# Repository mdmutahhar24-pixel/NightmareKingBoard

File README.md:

# NightmareKingBoard
A TKL Keyboard based of the Hollow Knight boss Nightmare King Grimm. (Very bad representation)

This keyboard features a red and black case, with RGB lighting, and a rotary encoder. This was coded with QMK firmware.

For more information, please check out the BOM or the Journals.

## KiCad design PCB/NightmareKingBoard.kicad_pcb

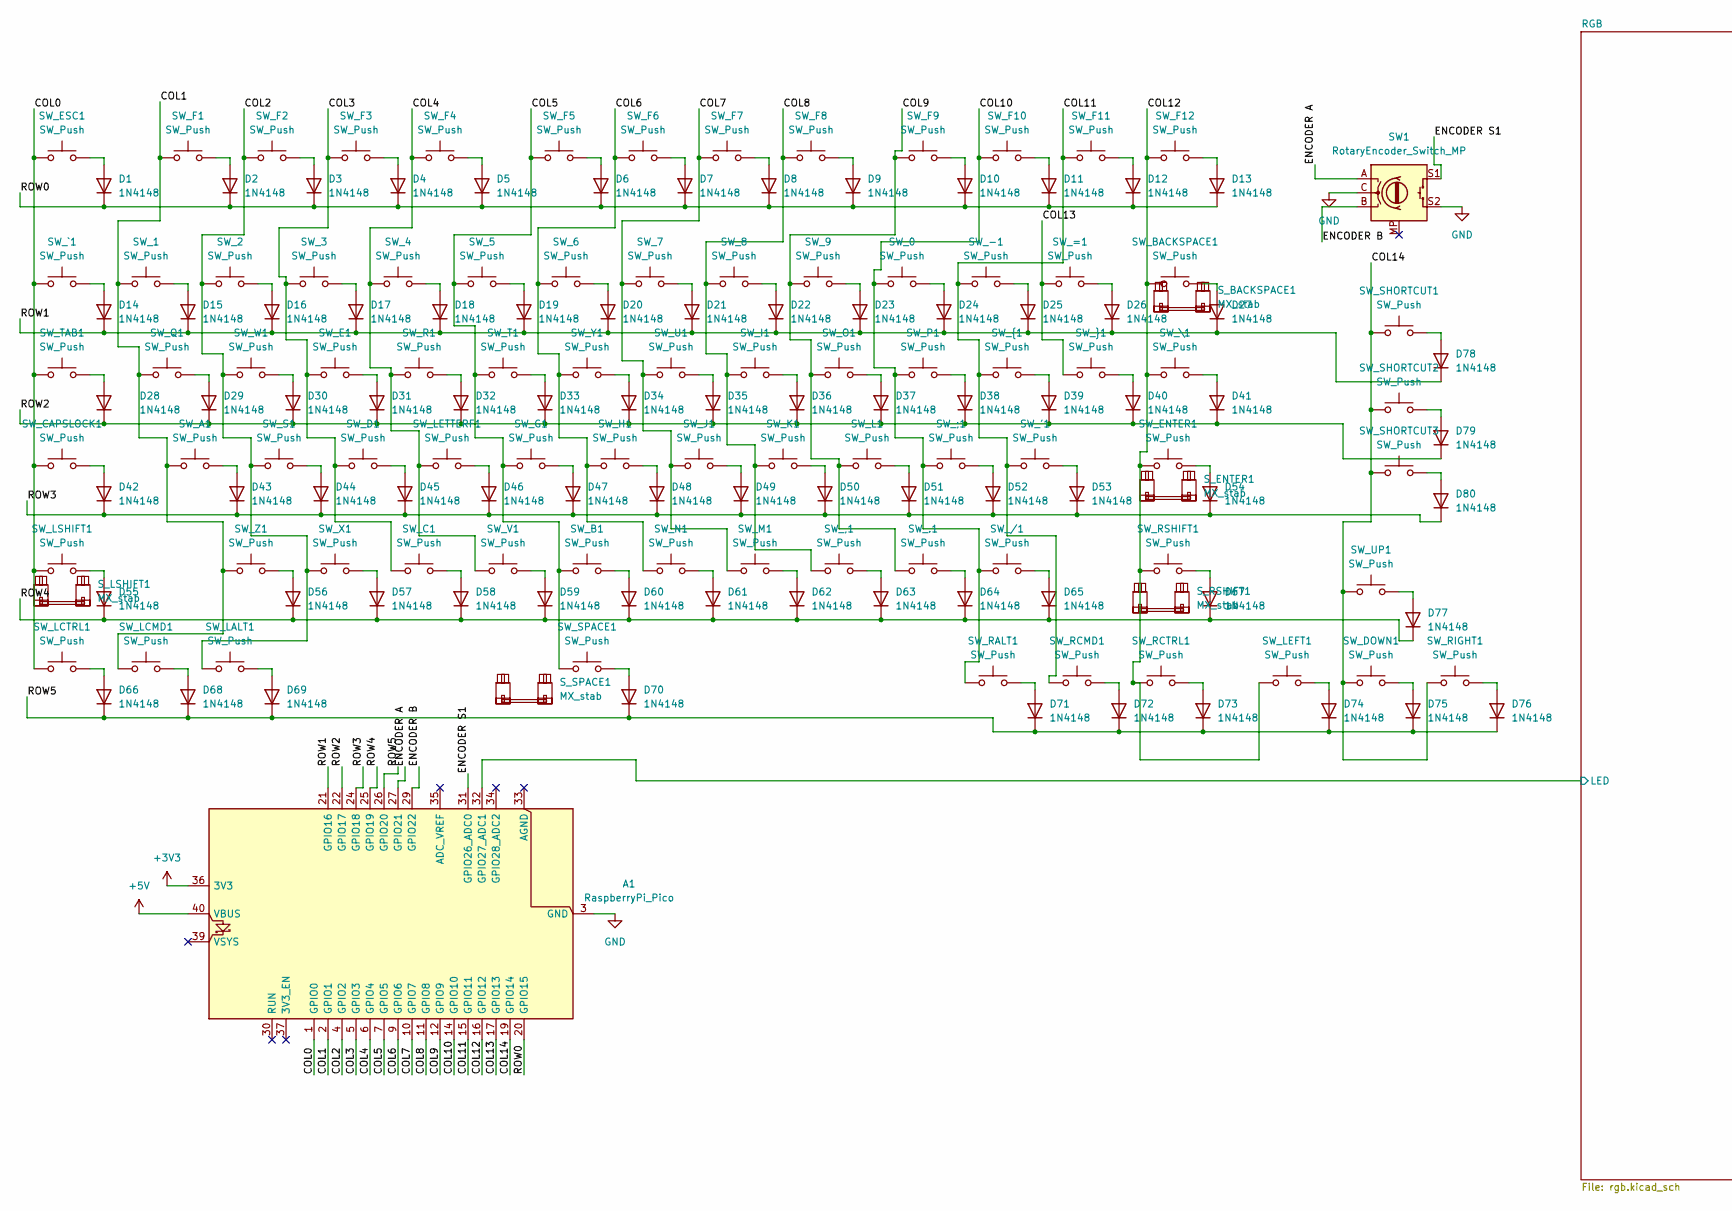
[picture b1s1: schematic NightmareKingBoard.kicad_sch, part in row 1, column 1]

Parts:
A1: RaspberryPi_Pico; RaspberryPi_Pico_Common_THT
D1, D2, D3, D4, D5, D6, D7, D8, D9, D10, D11, D12, D13, D14, D15, D16, D17, D18, D19, D20, D21, D22, D23, D24, D25, D26, D27, D28, D29, D30, D31, D32, D33, D34, D35, D36, D37, D38, D39, D40, D41, D42, D43, D44, D45, D46, D47, D48, D49, D50, D51, D52, D53, D54, D55, D56, D57, D58, D59, D60, D61, D62, D63, D64, D65, D66, D67, D68, D69, D70, D71, D72, D73, D74, D75, D76, D77, D78, D79, D80: 1N4148; D_DO-35_SOD27_P7.62mm_Horizontal
SW1: RotaryEncoder_Switch_MP; RotaryEncoder_Alps_EC11E-Switch_Vertical_H20mm
SW_0, SW_1, SW_2, SW_3, SW_4, SW_5, SW_6, SW_7, SW_8, SW_9, SW_.1: SW_Push; SW_MX_1u
SW_'1: SW_Push; SW_MX_1u
SW_,1: SW_Push; SW_MX_1u
SW_-1: SW_Push; SW_MX_1u
SW_/1: SW_Push; SW_MX_1u
SW_;1: SW_Push; SW_MX_1u
SW_=1: SW_Push; SW_MX_1u
SW_A1: SW_Push; SW_MX_1u
SW_B1: SW_Push; SW_MX_1u
SW_BACKSPACE1: SW_Push; SW_MX_1u
SW_C1: SW_Push; SW_MX_1u
SW_CAPSLOCK1: SW_Push; SW_MX_1.75u
SW_D1: SW_Push; SW_MX_1u
SW_DOWN1: SW_Push; SW_MX_1u
SW_E1: SW_Push; SW_MX_1u
SW_ENTER1: SW_Push; SW_MX_1u
SW_ESC1: SW_Push; SW_MX_1u
SW_F1, SW_F2, SW_F3, SW_F4, SW_F5, SW_F6, SW_F7, SW_F8, SW_F9, SW_F10, SW_F11, SW_F12: SW_Push; SW_MX_1u
SW_G1: SW_Push; SW_MX_1u
SW_H1: SW_Push; SW_MX_1u
SW_I1: SW_Push; SW_MX_1u
SW_J1: SW_Push; SW_MX_1u
SW_K1: SW_Push; SW_MX_1u
SW_L1: SW_Push; SW_MX_1u
SW_LALT1: SW_Push; SW_MX_1u
SW_LCMD1: SW_Push; SW_MX_1u
SW_LCTRL1: SW_Push; SW_MX_1u
SW_LEFT1: SW_Push; SW_MX_1u
SW_LETTERF1: SW_Push; SW_MX_1u
SW_LSHIFT1: SW_Push; SW_MX_1u
SW_M1: SW_Push; SW_MX_1u
SW_N1: SW_Push; SW_MX_1u
SW_O1: SW_Push; SW_MX_1u
SW_P1: SW_Push; SW_MX_1u
SW_Q1: SW_Push; SW_MX_1u
SW_R1: SW_Push; SW_MX_1u
SW_RALT1: SW_Push; SW_MX_1u
SW_RCMD1: SW_Push; SW_MX_1u
SW_RCTRL1: SW_Push; SW_MX_1u
SW_RIGHT1: SW_Push; SW_MX_1u
SW_RSHIFT1: SW_Push; SW_MX_1u
SW_S1: SW_Push; SW_MX_1u
SW_SHORTCUT1, SW_SHORTCUT2, SW_SHORTCUT3: SW_Push; SW_MX_1u
SW_SPACE1: SW_Push; SW_MX_1u
SW_T1: SW_Push; SW_MX_1u
SW_TAB1: SW_Push; SW_MX_1.5u
SW_U1: SW_Push; SW_MX_1u
SW_UP1: SW_Push; SW_MX_1u
SW_V1: SW_Push; SW_MX_1u
SW_W1: SW_Push; SW_MX_1u
SW_X1: SW_Push; SW_MX_1u
SW_Y1: SW_Push; SW_MX_1u
SW_Z1: SW_Push; SW_MX_1u
SW_\1: SW_Push; SW_MX_1u
SW_`1: SW_Push; SW_MX_1u
SW_{1: SW_Push; SW_MX_1u
SW_}1: SW_Push; SW_MX_1u
S_BACKSPACE1: MX_stab; STAB_MX_2u
S_ENTER1: MX_stab; STAB_MX_2.25u
S_LSHIFT1: MX_stab; STAB_MX_2.25u
S_RSHIFT1: MX_stab; STAB_MX_2.25u
S_SPACE1: MX_stab; STAB_MX_P_6.25u

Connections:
+3V3: A1.36 (3V3)
+5V: A1.40 (VBUS); also elsewhere on the board
/COL0: A1.1 (GPIO0), SW_CAPSLOCK1.1, SW_ESC1.1, SW_LCTRL1.1, SW_LSHIFT1.1, SW_TAB1.1, SW_`1.1
/COL1: A1.2 (GPIO1), SW_1.1, SW_A1.1, SW_F1.1, SW_LCMD1.1, SW_Q1.1, SW_Z1.1
/COL2: A1.4 (GPIO2), SW_2.1, SW_F2.1, SW_LALT1.1, SW_S1.1, SW_W1.1, SW_X1.1
/COL3: A1.5 (GPIO3), SW_3.1, SW_C1.1, SW_D1.1, SW_E1.1, SW_F3.1
/COL4: A1.6 (GPIO4), SW_4.1, SW_F4.1, SW_LETTERF1.1, SW_R1.1, SW_V1.1
/COL5: A1.7 (GPIO5), SW_5.1, SW_B1.1, SW_F5.1, SW_G1.1, SW_SPACE1.1, SW_T1.1
/COL6: A1.9 (GPIO6), SW_6.1, SW_F6.1, SW_H1.1, SW_N1.1, SW_Y1.1
/COL7: A1.10 (GPIO7), SW_7.1, SW_F7.1, SW_J1.1, SW_M1.1, SW_U1.1
/COL8: A1.11 (GPIO8), SW_8.1, SW_,1.1, SW_F8.1, SW_I1.1, SW_K1.1
/COL9: A1.12 (GPIO9), SW_9.1, SW_.1.1, SW_F9.1, SW_L1.1, SW_O1.1
/COL10: A1.14 (GPIO10), SW_0.1, SW_/1.1, SW_;1.1, SW_F10.1, SW_P1.1, SW_RALT1.1
/COL11: A1.15 (GPIO11), SW_'1.1, SW_-1.1, SW_F11.1, SW_RCMD1.1, SW_{1.1
/COL12: A1.16 (GPIO12), SW_BACKSPACE1.1, SW_ENTER1.1, SW_F12.1, SW_LEFT1.1, SW_RCTRL1.1, SW_RSHIFT1.1, SW_\1.1
/COL13: A1.17 (GPIO13), SW_=1.1, SW_}1.1
/COL14: A1.19 (GPIO14), SW_DOWN1.1, SW_RIGHT1.1, SW_SHORTCUT1.1, SW_SHORTCUT2.1, SW_SHORTCUT3.1, SW_UP1.1
/ENCODER A: A1.27 (GPIO21), SW1.A
/ENCODER B: A1.29 (GPIO22), SW1.B
/ENCODER S1: A1.31 (GPIO26_ADC0), SW1.S1
/RGB/LED: A1.32 (GPIO27_ADC1); also elsewhere on the board
/ROW0: A1.20 (GPIO15), D1.1 (K), D2.1 (K), D3.1 (K), D4.1 (K), D5.1 (K), D6.1 (K), D7.1 (K), D8.1 (K), D9.1 (K), D10.1 (K), D11.1 (K), D12.1 (K), D13.1 (K)
/ROW1: A1.21 (GPIO16), D14.1 (K), D15.1 (K), D16.1 (K), D17.1 (K), D18.1 (K), D19.1 (K), D20.1 (K), D21.1 (K), D22.1 (K), D23.1 (K), D24.1 (K), D25.1 (K), D26.1 (K), D27.1 (K), D78.1 (K)
/ROW2: A1.22 (GPIO17), D28.1 (K), D29.1 (K), D30.1 (K), D31.1 (K), D32.1 (K), D33.1 (K), D34.1 (K), D35.1 (K), D36.1 (K), D37.1 (K), D38.1 (K), D39.1 (K), D40.1 (K), D41.1 (K), D79.1 (K)
/ROW3: A1.24 (GPIO18), D42.1 (K), D43.1 (K), D44.1 (K), D45.1 (K), D46.1 (K), D47.1 (K), D48.1 (K), D49.1 (K), D50.1 (K), D51.1 (K), D52.1 (K), D53.1 (K), D54.1 (K), D80.1 (K)
/ROW4: A1.25 (GPIO19), D55.1 (K), D56.1 (K), D57.1 (K), D58.1 (K), D59.1 (K), D60.1 (K), D61.1 (K), D62.1 (K), D63.1 (K), D64.1 (K), D65.1 (K), D67.1 (K), D77.1 (K)
/ROW5: A1.26 (GPIO20), D66.1 (K), D68.1 (K), D69.1 (K), D70.1 (K), D71.1 (K), D72.1 (K), D73.1 (K), D74.1 (K), D75.1 (K), D76.1 (K)
GND: A1.3 (GND), A1.8 (GND), A1.13 (GND), A1.18 (GND), A1.23 (GND), A1.28 (GND), A1.38 (GND), SW1.C, SW1.S2; also elsewhere on the board
unnamed: D1.2 (A), SW_ESC1.2
unnamed: D2.2 (A), SW_F1.2
unnamed: D3.2 (A), SW_F2.2
unnamed: D4.2 (A), SW_F3.2
unnamed: D5.2 (A), SW_F4.2
unnamed: D6.2 (A), SW_F5.2
unnamed: D7.2 (A), SW_F6.2
unnamed: D8.2 (A), SW_F7.2
unnamed: D9.2 (A), SW_F8.2
unnamed: D10.2 (A), SW_F9.2
unnamed: D11.2 (A), SW_F10.2
unnamed: D12.2 (A), SW_F11.2
unnamed: D13.2 (A), SW_F12.2
unnamed: D14.2 (A), SW_`1.2
unnamed: D15.2 (A), SW_1.2
unnamed: D16.2 (A), SW_2.2
unnamed: D17.2 (A), SW_3.2
unnamed: D18.2 (A), SW_4.2
unnamed: D19.2 (A), SW_5.2
unnamed: D20.2 (A), SW_6.2
unnamed: D21.2 (A), SW_7.2
unnamed: D22.2 (A), SW_8.2
unnamed: D23.2 (A), SW_9.2
unnamed: D24.2 (A), SW_0.2
unnamed: D25.2 (A), SW_-1.2
unnamed: D26.2 (A), SW_=1.2
unnamed: D27.2 (A), SW_BACKSPACE1.2
unnamed: D28.2 (A), SW_TAB1.2
unnamed: D29.2 (A), SW_Q1.2
unnamed: D30.2 (A), SW_W1.2
unnamed: D31.2 (A), SW_E1.2
unnamed: D32.2 (A), SW_R1.2
unnamed: D33.2 (A), SW_T1.2
unnamed: D34.2 (A), SW_Y1.2
unnamed: D35.2 (A), SW_U1.2
unnamed: D36.2 (A), SW_I1.2
unnamed: D37.2 (A), SW_O1.2
unnamed: D38.2 (A), SW_P1.2
unnamed: D39.2 (A), SW_{1.2
unnamed: D40.2 (A), SW_}1.2
unnamed: D41.2 (A), SW_\1.2
unnamed: D42.2 (A), SW_CAPSLOCK1.2
unnamed: D43.2 (A), SW_A1.2
unnamed: D44.2 (A), SW_S1.2
unnamed: D45.2 (A), SW_D1.2
unnamed: D46.2 (A), SW_LETTERF1.2
unnamed: D47.2 (A), SW_G1.2
unnamed: D48.2 (A), SW_H1.2
unnamed: D49.2 (A), SW_J1.2
unnamed: D50.2 (A), SW_K1.2
unnamed: D51.2 (A), SW_L1.2
unnamed: D52.2 (A), SW_;1.2
unnamed: D53.2 (A), SW_'1.2
unnamed: D54.2 (A), SW_ENTER1.2
unnamed: D55.2 (A), SW_LSHIFT1.2
unnamed: D56.2 (A), SW_Z1.2
unnamed: D57.2 (A), SW_X1.2
unnamed: D58.2 (A), SW_C1.2
unnamed: D59.2 (A), SW_V1.2
unnamed: D60.2 (A), SW_B1.2
unnamed: D61.2 (A), SW_N1.2
unnamed: D62.2 (A), SW_M1.2
unnamed: D63.2 (A), SW_,1.2
unnamed: D64.2 (A), SW_.1.2
unnamed: D65.2 (A), SW_/1.2
unnamed: D66.2 (A), SW_LCTRL1.2
unnamed: D67.2 (A), SW_RSHIFT1.2
unnamed: D68.2 (A), SW_LCMD1.2
unnamed: D69.2 (A), SW_LALT1.2
unnamed: D70.2 (A), SW_SPACE1.2
unnamed: D71.2 (A), SW_RALT1.2
unnamed: D72.2 (A), SW_RCMD1.2
unnamed: D73.2 (A), SW_RCTRL1.2
unnamed: D74.2 (A), SW_LEFT1.2
unnamed: D75.2 (A), SW_DOWN1.2
unnamed: D76.2 (A), SW_RIGHT1.2
unnamed: D77.2 (A), SW_UP1.2
unnamed: D78.2 (A), SW_SHORTCUT1.2
unnamed: D79.2 (A), SW_SHORTCUT2.2
unnamed: D80.2 (A), SW_SHORTCUT3.2

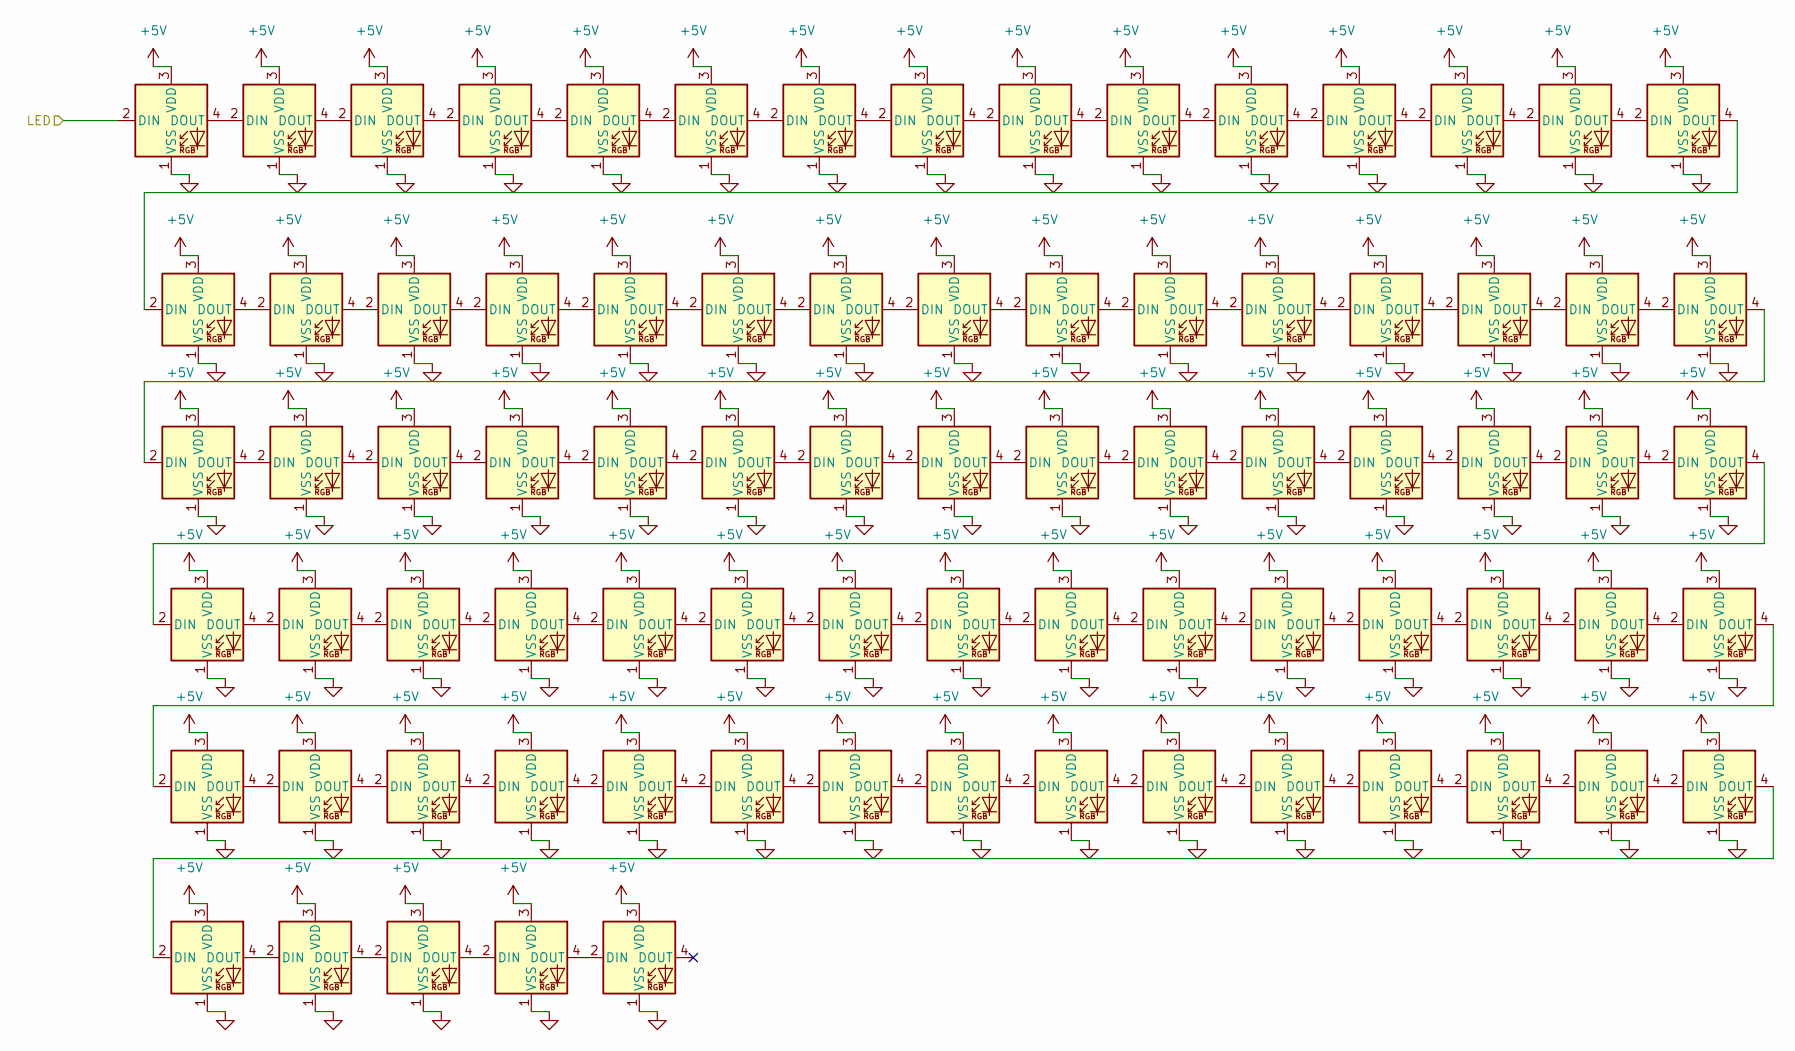
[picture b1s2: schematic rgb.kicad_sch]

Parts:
D81, D82, D83, D84, D85, D86, D87, D88, D89, D90, D91, D92, D93, D94, D95, D96, D97, D98, D99, D100, D101, D102, D103, D104, D105, D106, D107, D108, D109, D110, D111, D112, D113, D114, D115, D116, D117, D118, D119, D120, D121, D122, D123, D124, D125, D126, D127, D128, D129, D130, D131, D132, D133, D134, D135, D136, D137, D138, D139, D140, D141, D142, D143, D144, D145, D146, D147, D148, D149, D150, D151, D152, D153, D154, D155, D156, D157, D158, D159, D160: SK6812MINI-E; LED_SK6812MINI-E_3.2x2.8mm_P1.5mm_ReverseMount

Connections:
+5V: D81.3 (VDD), D82.3 (VDD), D83.3 (VDD), D84.3 (VDD), D85.3 (VDD), D86.3 (VDD), D87.3 (VDD), D88.3 (VDD), D89.3 (VDD), D90.3 (VDD), D91.3 (VDD), D92.3 (VDD), D93.3 (VDD), D94.3 (VDD), D95.3 (VDD), D96.3 (VDD), D97.3 (VDD), D98.3 (VDD), D99.3 (VDD), D100.3 (VDD), D101.3 (VDD), D102.3 (VDD), D103.3 (VDD), D104.3 (VDD), D105.3 (VDD), D106.3 (VDD), D107.3 (VDD), D108.3 (VDD), D109.3 (VDD), D110.3 (VDD), D111.3 (VDD), D112.3 (VDD), D113.3 (VDD), D114.3 (VDD), D115.3 (VDD), D116.3 (VDD), D117.3 (VDD), D118.3 (VDD), D119.3 (VDD), D120.3 (VDD), D121.3 (VDD), D122.3 (VDD), D123.3 (VDD), D124.3 (VDD), D125.3 (VDD), D126.3 (VDD), D127.3 (VDD), D128.3 (VDD), D129.3 (VDD), D130.3 (VDD), D131.3 (VDD), D132.3 (VDD), D133.3 (VDD), D134.3 (VDD), D135.3 (VDD), D136.3 (VDD), D137.3 (VDD), D138.3 (VDD), D139.3 (VDD), D140.3 (VDD), D141.3 (VDD), D142.3 (VDD), D143.3 (VDD), D144.3 (VDD), D145.3 (VDD), D146.3 (VDD), D147.3 (VDD), D148.3 (VDD), D149.3 (VDD), D150.3 (VDD), D151.3 (VDD), D152.3 (VDD), D153.3 (VDD), D154.3 (VDD), D155.3 (VDD), D156.3 (VDD), D157.3 (VDD), D158.3 (VDD), D159.3 (VDD), D160.3 (VDD); also elsewhere on the board
/RGB/LED: D81.2 (DIN); also elsewhere on the board
GND: D81.1 (VSS), D82.1 (VSS), D83.1 (VSS), D84.1 (VSS), D85.1 (VSS), D86.1 (VSS), D87.1 (VSS), D88.1 (VSS), D89.1 (VSS), D90.1 (VSS), D91.1 (VSS), D92.1 (VSS), D93.1 (VSS), D94.1 (VSS), D95.1 (VSS), D96.1 (VSS), D97.1 (VSS), D98.1 (VSS), D99.1 (VSS), D100.1 (VSS), D101.1 (VSS), D102.1 (VSS), D103.1 (VSS), D104.1 (VSS), D105.1 (VSS), D106.1 (VSS), D107.1 (VSS), D108.1 (VSS), D109.1 (VSS), D110.1 (VSS), D111.1 (VSS), D112.1 (VSS), D113.1 (VSS), D114.1 (VSS), D115.1 (VSS), D116.1 (VSS), D117.1 (VSS), D118.1 (VSS), D119.1 (VSS), D120.1 (VSS), D121.1 (VSS), D122.1 (VSS), D123.1 (VSS), D124.1 (VSS), D125.1 (VSS), D126.1 (VSS), D127.1 (VSS), D128.1 (VSS), D129.1 (VSS), D130.1 (VSS), D131.1 (VSS), D132.1 (VSS), D133.1 (VSS), D134.1 (VSS), D135.1 (VSS), D136.1 (VSS), D137.1 (VSS), D138.1 (VSS), D139.1 (VSS), D140.1 (VSS), D141.1 (VSS), D142.1 (VSS), D143.1 (VSS), D144.1 (VSS), D145.1 (VSS), D146.1 (VSS), D147.1 (VSS), D148.1 (VSS), D149.1 (VSS), D150.1 (VSS), D151.1 (VSS), D152.1 (VSS), D153.1 (VSS), D154.1 (VSS), D155.1 (VSS), D156.1 (VSS), D157.1 (VSS), D158.1 (VSS), D159.1 (VSS), D160.1 (VSS); also elsewhere on the board
unnamed: D81.4 (DOUT), D82.2 (DIN)
unnamed: D82.4 (DOUT), D83.2 (DIN)
unnamed: D83.4 (DOUT), D84.2 (DIN)
unnamed: D84.4 (DOUT), D85.2 (DIN)
unnamed: D85.4 (DOUT), D86.2 (DIN)
unnamed: D86.4 (DOUT), D87.2 (DIN)
unnamed: D87.4 (DOUT), D88.2 (DIN)
unnamed: D88.4 (DOUT), D89.2 (DIN)
unnamed: D89.4 (DOUT), D90.2 (DIN)
unnamed: D90.4 (DOUT), D91.2 (DIN)
unnamed: D91.4 (DOUT), D92.2 (DIN)
unnamed: D92.4 (DOUT), D93.2 (DIN)
unnamed: D93.4 (DOUT), D94.2 (DIN)
unnamed: D94.4 (DOUT), D95.2 (DIN)
unnamed: D95.4 (DOUT), D96.2 (DIN)
unnamed: D96.4 (DOUT), D97.2 (DIN)
unnamed: D97.4 (DOUT), D98.2 (DIN)
unnamed: D98.4 (DOUT), D99.2 (DIN)
unnamed: D99.4 (DOUT), D100.2 (DIN)
unnamed: D100.4 (DOUT), D101.2 (DIN)
unnamed: D101.4 (DOUT), D102.2 (DIN)
unnamed: D102.4 (DOUT), D103.2 (DIN)
unnamed: D103.4 (DOUT), D104.2 (DIN)
unnamed: D104.4 (DOUT), D105.2 (DIN)
unnamed: D105.4 (DOUT), D106.2 (DIN)
unnamed: D106.4 (DOUT), D107.2 (DIN)
unnamed: D107.4 (DOUT), D108.2 (DIN)
unnamed: D108.4 (DOUT), D109.2 (DIN)
unnamed: D109.4 (DOUT), D110.2 (DIN)
unnamed: D110.4 (DOUT), D111.2 (DIN)
unnamed: D111.4 (DOUT), D112.2 (DIN)
unnamed: D112.4 (DOUT), D113.2 (DIN)
unnamed: D113.4 (DOUT), D114.2 (DIN)
unnamed: D114.4 (DOUT), D115.2 (DIN)
unnamed: D115.4 (DOUT), D116.2 (DIN)
unnamed: D116.4 (DOUT), D117.2 (DIN)
unnamed: D117.4 (DOUT), D118.2 (DIN)
unnamed: D118.4 (DOUT), D119.2 (DIN)
unnamed: D119.4 (DOUT), D120.2 (DIN)
unnamed: D120.4 (DOUT), D121.2 (DIN)
unnamed: D121.4 (DOUT), D122.2 (DIN)
unnamed: D122.4 (DOUT), D123.2 (DIN)
unnamed: D123.4 (DOUT), D124.2 (DIN)
unnamed: D124.4 (DOUT), D125.2 (DIN)
unnamed: D125.4 (DOUT), D126.2 (DIN)
unnamed: D126.4 (DOUT), D127.2 (DIN)
unnamed: D127.4 (DOUT), D128.2 (DIN)
unnamed: D128.4 (DOUT), D129.2 (DIN)
unnamed: D129.4 (DOUT), D130.2 (DIN)
unnamed: D130.4 (DOUT), D131.2 (DIN)
unnamed: D131.4 (DOUT), D132.2 (DIN)
unnamed: D132.4 (DOUT), D133.2 (DIN)
unnamed: D133.4 (DOUT), D134.2 (DIN)
unnamed: D134.4 (DOUT), D135.2 (DIN)
unnamed: D135.4 (DOUT), D136.2 (DIN)
unnamed: D136.4 (DOUT), D137.2 (DIN)
unnamed: D137.4 (DOUT), D138.2 (DIN)
unnamed: D138.4 (DOUT), D139.2 (DIN)
unnamed: D139.4 (DOUT), D140.2 (DIN)
unnamed: D140.4 (DOUT), D141.2 (DIN)
unnamed: D141.4 (DOUT), D142.2 (DIN)
unnamed: D142.4 (DOUT), D143.2 (DIN)
unnamed: D143.4 (DOUT), D144.2 (DIN)
unnamed: D144.4 (DOUT), D145.2 (DIN)
unnamed: D145.4 (DOUT), D146.2 (DIN)
unnamed: D146.4 (DOUT), D147.2 (DIN)
unnamed: D147.4 (DOUT), D148.2 (DIN)
unnamed: D148.4 (DOUT), D149.2 (DIN)
unnamed: D149.4 (DOUT), D150.2 (DIN)
unnamed: D150.4 (DOUT), D151.2 (DIN)
unnamed: D151.4 (DOUT), D152.2 (DIN)
unnamed: D152.4 (DOUT), D153.2 (DIN)
unnamed: D153.4 (DOUT), D154.2 (DIN)
unnamed: D154.4 (DOUT), D155.2 (DIN)
unnamed: D155.4 (DOUT), D156.2 (DIN)
unnamed: D156.4 (DOUT), D157.2 (DIN)
unnamed: D157.4 (DOUT), D158.2 (DIN)
unnamed: D158.4 (DOUT), D159.2 (DIN)
unnamed: D159.4 (DOUT), D160.2 (DIN)

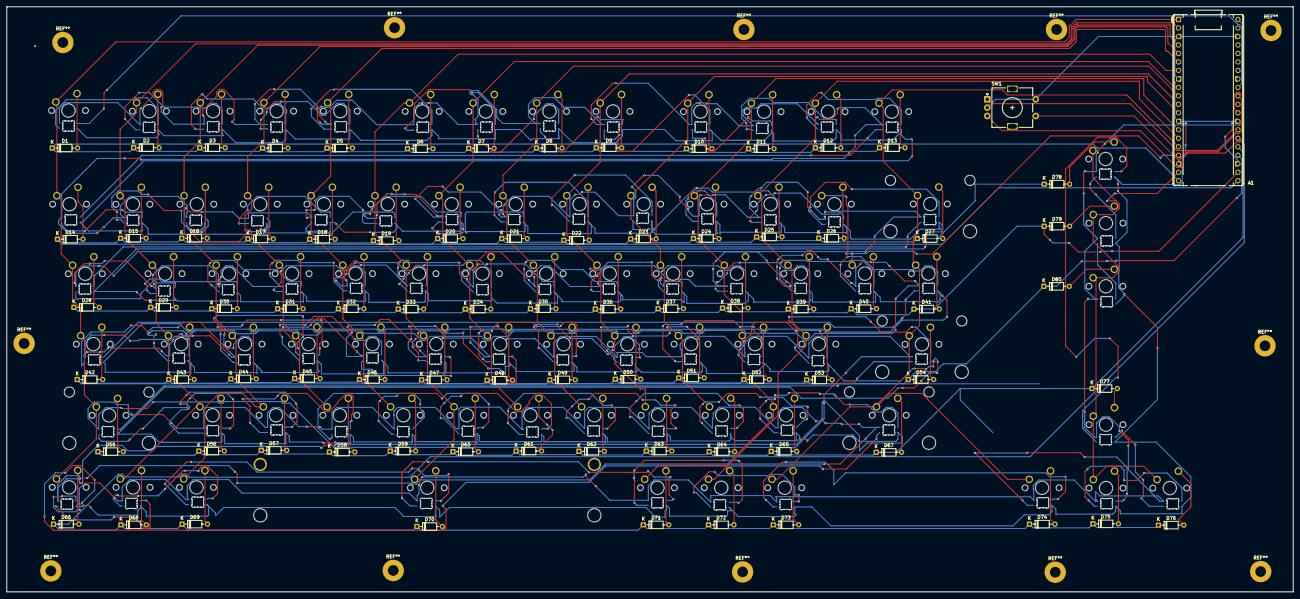
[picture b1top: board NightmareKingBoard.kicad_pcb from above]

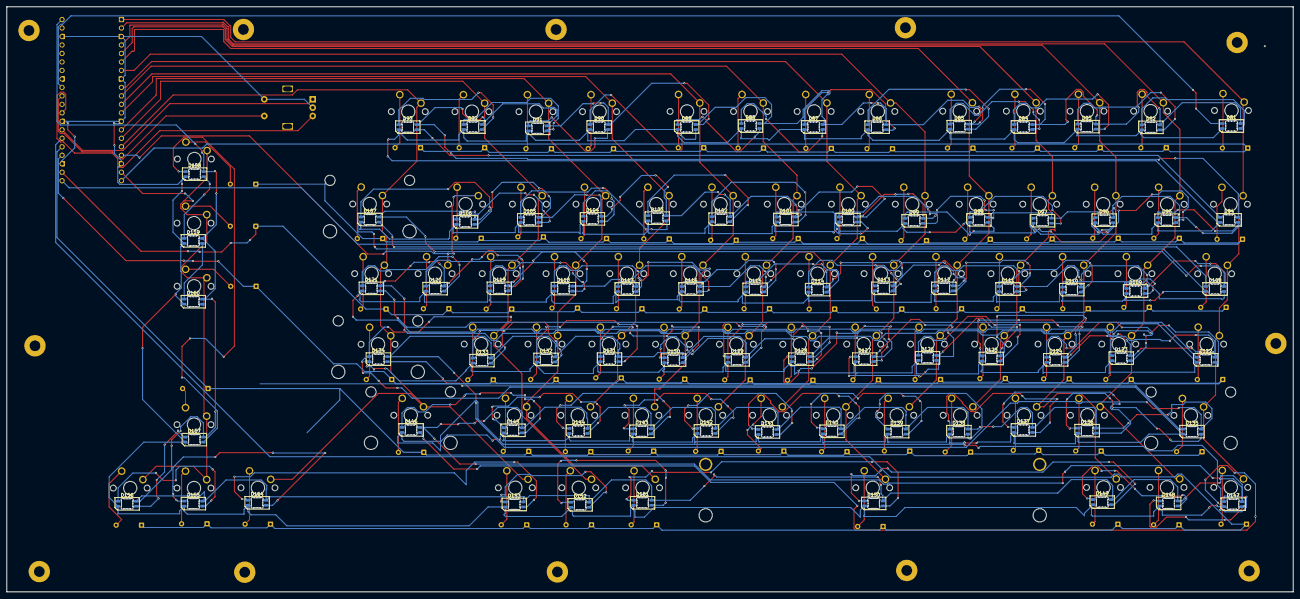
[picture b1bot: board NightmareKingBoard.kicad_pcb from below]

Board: 2 copper layers, 385.2 x 175.2 mm, 247 parts (80 on the bottom side), 186 nets.
